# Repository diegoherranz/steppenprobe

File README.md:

# Steppenprobe
Open Source Hardware JTAG/SWD/UART/SWO interface board

https://github.com/diegoherranz/steppenprobe

## Basic specs:

- Open Source Hardware and designed in [KiCad](https://kicad.org).
- [FT2232H](https://ftdichip.com/products/ft2232hl)-based
- Simultaneous operation of JTAG/SWD and UART/SWO.
- STDC14 connector: standard Arm Cortex debug connector (1.27 mm pitch) with extra pins for UART. JTAG/SWD and UART on a single connector while being compatible with the standard Arm Cortex debug connector (middle 10 pins).
- USB powered: no power supply needed.
- USB type-C receptacle: more convenient (reversible) and future-proof (it should be the most common connector during the next few years).
- OpenOCD compatible, supported from version 0.11.0 (older versions can be used by adapting this [config file](https://sourceforge.net/p/openocd/code/ci/master/tree/tcl/interface/ftdi/steppenprobe.cfg) to the old sintax).
- JTAG or SWD use without any jumper or switch operation required (configured from OpenOCD).
- Switch-selectable UART RX or SWO operation.
- Signals also available on 2.54 mm pin header to work with any custom pinout.
- 4 GPIO.
- System Reset tactile switch.
- I/O buffers for protection and to be able to use a wide voltage range (1.65 V to 5.5 V).
- Descriptive LED indicators.

## Schematic PDF, Gerbers and other generated files:
See [releases](https://github.com/diegoherranz/steppenprobe/releases).

## FTDI channels

The FT2232H has 2 independent channels. In this board:

- Channel A: Used for JTAG or SWD (MPSSE mode) + GPIOs
- Channel B: Used as UART. TX+RX or TX+SWO depending on the position of the physical switch.

After enumeration, both channels will default to UART mode, so on a Linux system they will show up as `/dev/ttyUSB0` and `/dev/ttyUSB1`. When channel A gets reconfigured to MPSSE mode (e.g. when using OpenOCD with it), then `/dev/ttyUSB0` will disappear and channel B will remain as `/dev/ttyUSB1`.

## 3D renders

## Options for J2 connector (1.27 mm pitch header)
You can solder a 10-way or 14-way header depending on what suits you best:
 - 10-way header: [FTSH-105-01-F-DV-K](https://www.samtec.com/products/ftsh-105-01-f-dv-k) or equivalent. Use the central 10 pads in this case. JTAG, SWD, SWO and RESET (Arm Cortex debug connector standard).
 - 14-way header: [FTSH-107-01-F-DV-K](https://www.samtec.com/products/ftsh-107-01-f-dv-k) or equivalent. Compared to the 10 pin option, it adds UART TX and RX (STDC14 standard). This can still connect to targets with a 10-way header by using a 14-way to 10-way cable.

## OpenOCD example commands

### Flashing
Flashing [NuttX](https://nuttx.apache.org) to a [Blue Pill](https://stm32-base.org/boards/STM32F103C8T6-Blue-Pill.html) using JTAG:

```
openocd -f interface/ftdi/steppenprobe.cfg -f target/stm32f1x.cfg -c "program nuttx.bin 0x08000000 verify reset exit"
```

Same but using SWD:

```
openocd -f interface/ftdi/steppenprobe.cfg -c "transport select swd" -f target/stm32f1x.cfg -c "program nuttx.bin 0x08000000 verify reset exit"
```
All these examples use the default reset signals configuration. You may need to adjust it for your target board to work or even if it works, you may want to define it explicitely. See the [Reset Configuration chapter](http://openocd.org/doc-release/html/Reset-Configuration.html) of the OpenOCD documentation for more details.

You can do so directly on the OpenOCD command:

```
openocd -f interface/ftdi/steppenprobe.cfg -c "reset_config srst_only" -f target/stm32f1x.cfg -c "program nuttx.bin 0x08000000 verify reset exit"
```

or defining your board config file (your_board.cfg) which may look like this:

```
reset_config srst_only
source [find target/stm32f4x.cfg]
```

And then you do:

```
openocd -f interface/ftdi/steppenprobe.cfg -f your_board.cfg -c "program nuttx.bin 0x08000000 verify reset exit"
```

### Debugging
Debugging example for an STM32F4 target.

Start OpenOCD:
- JTAG: `openocd -f interface/ftdi/steppenprobe.cfg -f target/stm32f4x.cfg`
- SWD: `openocd -f interface/ftdi/steppenprobe.cfg -c "transport select swd" -f target/stm32f4x.cfg
`

On a different terminal:
```
$ gdb-multiarch your_code.elf # or gcc-arm-none-eabi depending on your system.

# Attach to OpenOCD
(gdb) target extended-remote localhost:3333

# Reset the boad
(gdb) monitor reset halt

# Load the code to flash
(gdb) load

# Start running
continue
```
Then use GDB as normal: see https://www.gnu.org/software/gdb/documentation/

### Debugging + SWO

Start OpenOCD in SWD mode and use the `tpiu config` command. Also, the UART switch should be in the "TX+SWO" position.

```
openocd -f interface/ftdi/steppenprobe.cfg -c "transport select swd" -f target/stm32f4x.cfg -c "tpiu config external uart off 168000000 115200"
```

The `tpiu config` command configures the ARM ITM module and the SWO output. In the command above, `16800000` represents the TRACECLKIN frequency (usually the same as HCLK), and `115200` is the frequency/baurate of the SWO line. Adjust both as desired. See the [OpenOCD documentation](http://openocd.org/doc-release/html/Architecture-and-Core-Commands.html#ARMv7_002dM-specific-commands
) for more info.

If the selected SWO frequency can't be achieved, OpenOCD will output a message like:

> Info : Can not obtain 115200 trace port frequency from 168000000 TRACECLKIN frequency, using 115147 instead

In this case, the frequency achieved is close enough, but pay attention in case it wasn't.

Then, on another terminal:
```
# configure the serial port speed
stty -F /dev/ttyUSB1 115200

# start the ITM decoder
./itmdump -f /dev/ttyUSB1 -d1 
```

Note: ITM decoder available [here](https://sourceforge.net/p/openocd/code/ci/master/tree/contrib/itmdump.c), just compile by doing `gcc itmdump.c -o itmdump`.

One of the advantages of using the SWO signal is that it can be faster than a standard UART, specially for slow core clock frequencies (see [this nice article](https://blog.japaric.io/itm/) for more info). To benefit from that, we need to use faster SWO frequencies.

The FT2232H is capable or running the UART up to 12 Mbps, but the configuration is more cumbersome for the fastest speeds.

On a recent Linux system, you can go up to 4 Mbps, configuring everything the same way as explained above for 115200 bps. On different OSes, you may not be able to go above 115200 bps or even 38400 bps.

For 4 Mbps:

```
openocd -f interface/ftdi/steppenprobe.cfg -c "transport select swd" -f target/stm32f4x.cfg -c "tpiu config external uart off 168000000 4000000"
```

On another terminal:
```
stty -F /dev/ttyUSB1 4000000
./itmdump -f /dev/ttyUSB1 -d1
```

To use even higher frequencies, up to the maximum of 12 MHz if your setup and cabling allows it, it's necessary to use setserial to alias 38400 bps to a custom divider. The base frequency of the FT2232H is 60 MHz, so for instance, for 12 MHz, the divisor must be set to 5.

```
openocd -f interface/ftdi/steppenprobe.cfg -c "transport select swd" -f target/stm32f4x.cfg -c "tpiu config external uart off 168000000 12000000"
```

On a different terminal:
```
setserial /dev/ttyUSB1 spd_cust divisor 5
stty -F /dev/ttyUSB1 38400
./itmdump -f /dev/ttyUSB1 -d1
```

### GPIO usage
There are 4 GPIOs available: GPIO_A to GPIO_D. By default they are High-Impedance (Z).

They can be set through OpenOCD by using `ftdi_set_signal name 0|1|z`. For example:
```
ftdi_set_signal GPIO_B 1
```

And similarly, they can be read using `ftdi_get_signal name`.

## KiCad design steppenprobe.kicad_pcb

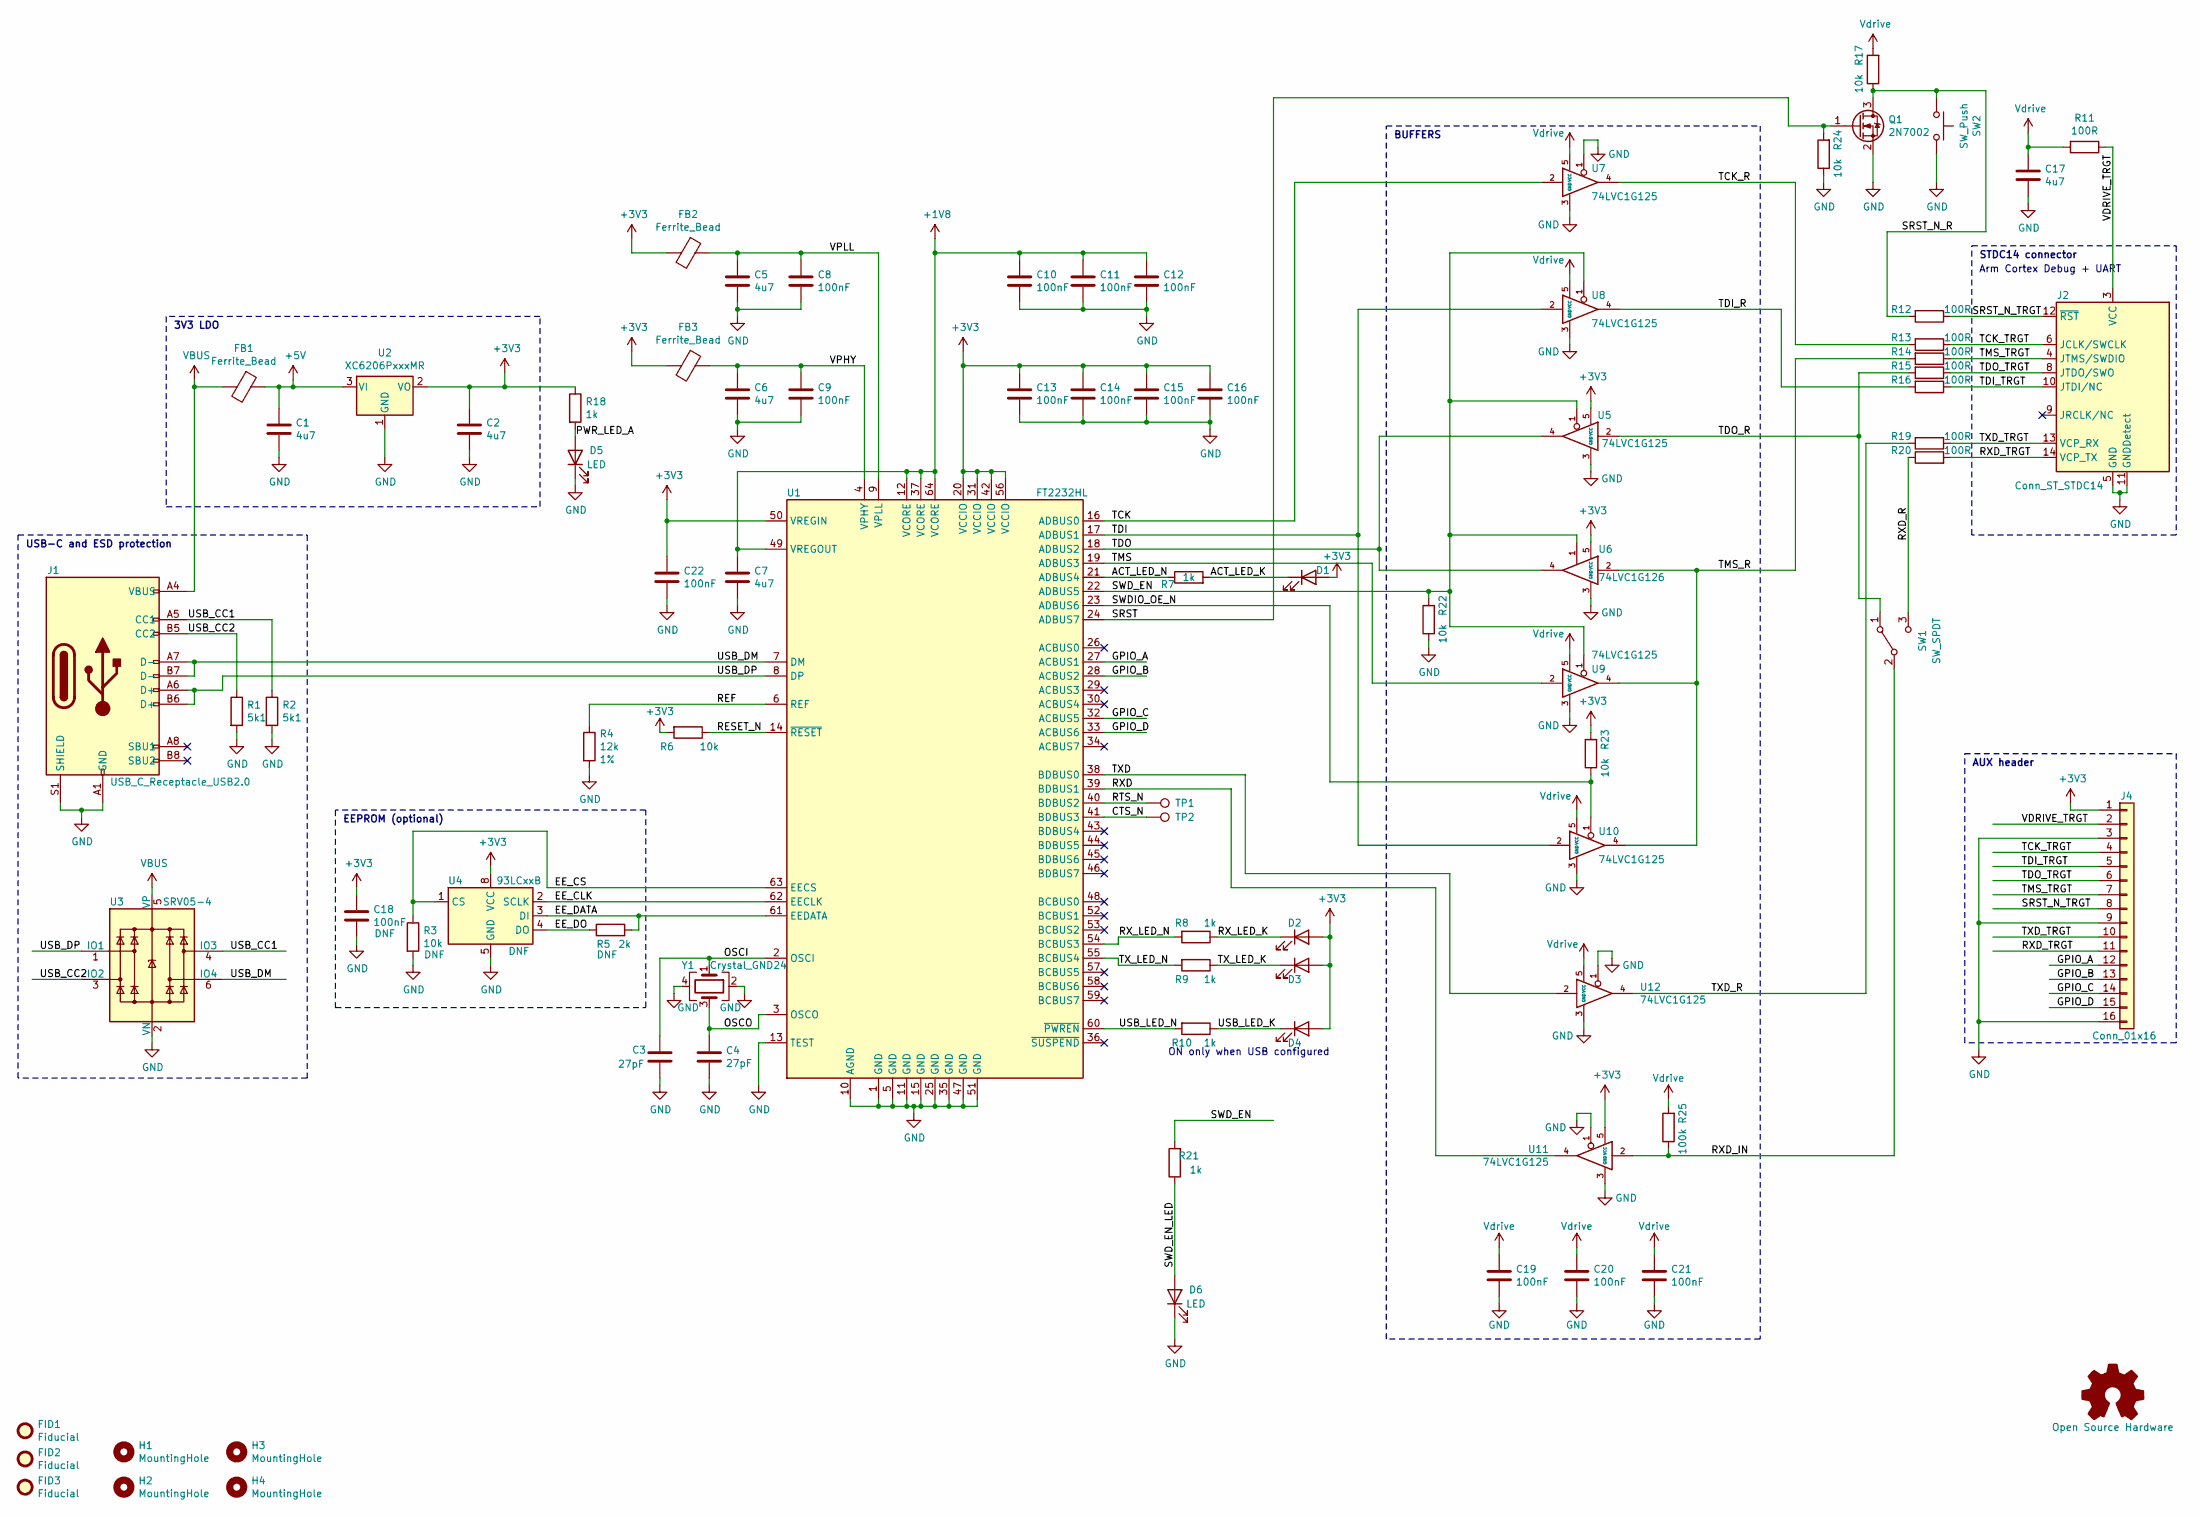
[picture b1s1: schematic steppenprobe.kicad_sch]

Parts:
C1, C2, C5, C6, C7, C17: 4u7; C_0603_1608Metric; Tolerance 10%; MPN CL10A475KO8NNNC; LCSC_PN C19666
C3, C4: 27pF; C_0603_1608Metric; Tolerance 5%; MPN C0603C270J5GAC; LCSC_PN C1656
C8, C9, C10, C11, C12, C13, C14, C15, C16, C19, C20, C21, C22: 100nF; C_0603_1608Metric; Tolerance 10%; MPN CC0603KRX7R9BB104; LCSC_PN C14663
C18: 100nF; C_0603_1608Metric
D1, D2, D3, D4, D5, D6: LED; LED_0603_1608Metric; MPN 19-217/GHC-YR1S2/3T; LCSC_PN C72043
FB1, FB2, FB3: Ferrite_Bead; L_0603_1608Metric; MPN2 BKP1608HS121-T; LCSC_PN C85831
FID1, FID2, FID3: Fiducial; Fiducial_1mm_Mask2mm
H1, H2, H3, H4: MountingHole; MountingHole_3.2mm_M3
J1: USB_C_Receptacle_USB2.0; USB_C_Receptacle_GCT_USB4085; MPN USB4085-GF-A
J2: Conn_ST_STDC14; PinHeader_2x07_P1.27mm_Vertical_SMD; MPN FTSH-107-01-F-DV-K (if 14-way)
J4: Conn_01x16; PinHeader_1x16_P2.54mm_Vertical; MPN M20-9991645
LOGO1: Open Source Hardware; OSHW-Logo_7.5x8mm_SilkScreen
Q1: 2N7002; SOT-23; MPN 2N7002-7-F; LCSC_PN C8545
R1, R2: 5k1; R_0603_1608Metric; Tolerance 5%; LCSC_PN C23186
R3: 10k; R_0603_1608Metric
R4: 12k; R_0603_1608Metric; Tolerance 1%; LCSC_PN C22790
R5: 2k; R_0603_1608Metric
R6, R17, R22, R23, R24: 10k; R_0603_1608Metric; Tolerance 5%; LCSC_PN C25804
R7, R8, R9, R10, R18, R21: 1k; R_0603_1608Metric; Tolerance 5%; LCSC_PN C21190
R11, R12, R13, R14, R15, R16, R19, R20: 100R; R_0603_1608Metric; Tolerance 5%; LCSC_PN C22775
R25: 100k; R_0603_1608Metric; Tolerance 5%; LCSC_PN C25803
SW1: SW_SPDT; SW_SPDT_PCM12; MPN EG1215AA
SW2: SW_Push; SW_Push_1P1T_NO_E-Switch_TL3301NxxxxxG; MPN PTS645SK43SMTR92 LFS
TP1, TP2: TestPoint; TestPoint_Pad_D1.0mm
U1: FT2232HL; LQFP-64_10x10mm_P0.5mm; MPN FT2232HL; LCSC_PN C27882
U2: XC6206PxxxMR; SOT-23; MPN XC6206P332MR; LCSC_PN C5446
U3: SRV05-4; SOT-23-6; MPN2 SRV05-4-P-T7; LCSC_PN C85364
U4: 93LCxxB; SOIC-8_3.9x4.9mm_P1.27mm
U5, U7, U8, U9, U10, U11, U12: 74LVC1G125; SOT-353_SC-70-5; MPN 74LVC1G125GW,125; LCSC_PN C12519
U6: 74LVC1G126; SOT-353_SC-70-5; MPN 74LVC1G126GW,125; LCSC_PN C55052
Y1: Crystal_GND24; Crystal_SMD_3225-4Pin_3.2x2.5mm; Tolerance 10PPM; MPN ABM8-12.000MHZ-20-B1U-T; LCSC_PN C9002

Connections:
+1V8: C7.1, C10.1, C11.1, C12.1, U1.12 (VCORE), U1.37 (VCORE), U1.49 (VREGOUT), U1.64 (VCORE)
+3V3: C2.1, C13.1, C14.1, C15.1, C16.1, C18.1, C22.1, D1.2 (A), D2.2 (A), D3.2 (A), D4.2 (A), FB2.2, FB3.2, J4.1, R6.2, R18.1, R23.2, U1.20 (VCCIO), U1.31 (VCCIO), U1.42 (VCCIO), U1.50 (VREGIN), U1.56 (VCCIO), U2.2 (VO), U4.8 (VCC), U5.5 (VCC), U6.5 (VCC), U11.5 (VCC)
+5V: C1.1, FB1.1, U2.3 (VI)
/ACT_LED_K: D1.1 (K), R7.2
/ACT_LED_N: R7.1, U1.21 (ADBUS4)
/CTS_N: TP2.1, U1.41 (BDBUS3)
/EE_CLK: U1.62 (EECLK), U4.2 (SCLK)
/EE_CS: R3.1, U1.63 (EECS), U4.1 (CS)
/EE_DATA: R5.2, U1.61 (EEDATA), U4.3 (DI)
/EE_DO: R5.1, U4.4 (DO)
/GPIO_A: J4.12, U1.27 (ACBUS1)
/GPIO_B: J4.13, U1.28 (ACBUS2)
/GPIO_C: J4.14, U1.32 (ACBUS5)
/GPIO_D: J4.15, U1.33 (ACBUS6)
/OSCI: C3.1, U1.2 (OSCI), Y1.1
/OSCO: C4.1, U1.3 (OSCO), Y1.3
/PWR_LED_A: D5.2 (A), R18.2
/REF: R4.1, U1.6 (REF)
/RESET_N: R6.1, U1.14 (~RESET)
/RTS_N: TP1.1, U1.40 (BDBUS2)
/RXD: U1.39 (BDBUS1), U11.4
/RXD_IN: R25.1, SW1.2 (B), U11.2
/RXD_R: R20.1, SW1.3 (C)
/RXD_TRGT: J2.14 (VCP_TX), J4.11, R20.2
/RX_LED_K: D2.1 (K), R8.1
/RX_LED_N: R8.2, U1.54 (BCBUS3)
/SRST: Q1.1 (G), R24.2, U1.24 (ADBUS7)
/SRST_N_R: Q1.3 (D), R12.2, R17.1, SW2.1
/SRST_N_TRGT: J2.12 (~RST), J4.8, R12.1
/SWDIO_OE_N: R23.1, U1.23 (ADBUS6), U10.1
/SWD_EN: R21.2, R22.2, U1.22 (ADBUS5), U5.1, U6.1, U8.1, U9.1
/SWD_EN_LED: D6.2 (A), R21.1
/TCK: U1.16 (ADBUS0), U7.2
/TCK_R: R13.2, U7.4
/TCK_TRGT: J2.6 (JCLK/SWCLK), J4.4, R13.1
/TDI: U1.17 (ADBUS1), U8.2, U10.2
/TDI_R: R16.2, U8.4
/TDI_TRGT: J2.10 (JTDI/NC), J4.5, R16.1
/TDO: U1.18 (ADBUS2), U5.4, U6.4
/TDO_R: R15.2, SW1.1 (A), U5.2
/TDO_TRGT: J2.8 (JTDO/SWO), J4.6, R15.1
/TMS: U1.19 (ADBUS3), U9.2
/TMS_R: R14.2, U6.2, U9.4, U10.4
/TMS_TRGT: J2.4 (JTMS/SWDIO), J4.7, R14.1
/TXD: U1.38 (BDBUS0), U12.2
/TXD_R: R19.2, U12.4
/TXD_TRGT: J2.13 (VCP_RX), J4.10, R19.1
/TX_LED_K: D3.1 (K), R9.1
/TX_LED_N: R9.2, U1.55 (BCBUS4)
/USB_CC1: J1.A5 (CC1), R2.1, U3.4 (IO3)
/USB_CC2: J1.B5 (CC2), R1.1, U3.3 (IO2)
/USB_DM: J1.A7 (D-), J1.B7 (D-), U1.7 (DM), U3.6 (IO4)
/USB_DP: J1.A6 (D+), J1.B6 (D+), U1.8 (DP), U3.1 (IO1)
/USB_LED_K: D4.1 (K), R10.1
/USB_LED_N: R10.2, U1.60 (~PWREN)
/VDRIVE_TRGT: J2.3 (VCC), J4.2, R11.1
/VPHY: C6.1, C9.1, FB3.1, U1.4 (VPHY)
/VPLL: C5.1, C8.1, FB2.1, U1.9 (VPLL)
GND: C1.2, C2.2, C3.2, C4.2, C5.2, C6.2, C7.2, C8.2, C9.2, C10.2, C11.2, C12.2, C13.2, C14.2, C15.2, C16.2, C17.2, C18.2, C19.2, C20.2, C21.2, C22.2, D5.1 (K), D6.1 (K), J1.A1 (GND), J1.A12 (GND), J1.B1 (GND), J1.B12 (GND), J1.S1 (SHIELD), J2.5 (GND), J2.7 (GND), J2.11 (GNDDetect), J4.3, J4.9, J4.16, Q1.2 (S), R1.2, R2.2, R3.2, R4.2, R22.1, R24.1, SW2.2, U1.1 (GND), U1.5 (GND), U1.10 (AGND), U1.11 (GND), U1.13 (TEST), U1.15 (GND), U1.25 (GND), U1.35 (GND), U1.47 (GND), U1.51 (GND), U2.1 (GND), U3.2 (VN), U4.5 (GND), U5.3 (GND), U6.3 (GND), U7.1, U7.3 (GND), U8.3 (GND), U9.3 (GND), U10.3 (GND), U11.1, U11.3 (GND), U12.1, U12.3 (GND), Y1.2, Y1.4
VBUS: FB1.2, J1.A4 (VBUS), J1.A9 (VBUS), J1.B4 (VBUS), J1.B9 (VBUS), U3.5 (VP)
Vdrive: C17.1, C19.1, C20.1, C21.1, R11.2, R17.2, R25.2, U7.5 (VCC), U8.5 (VCC), U9.5 (VCC), U10.5 (VCC), U12.5 (VCC)

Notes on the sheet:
EEPROM (optional)
ON only when USB configured
Arm Cortex Debug + UART
3V3 LDO
AUX header
STDC14 connector
USB-C and ESD protection
BUFFERS

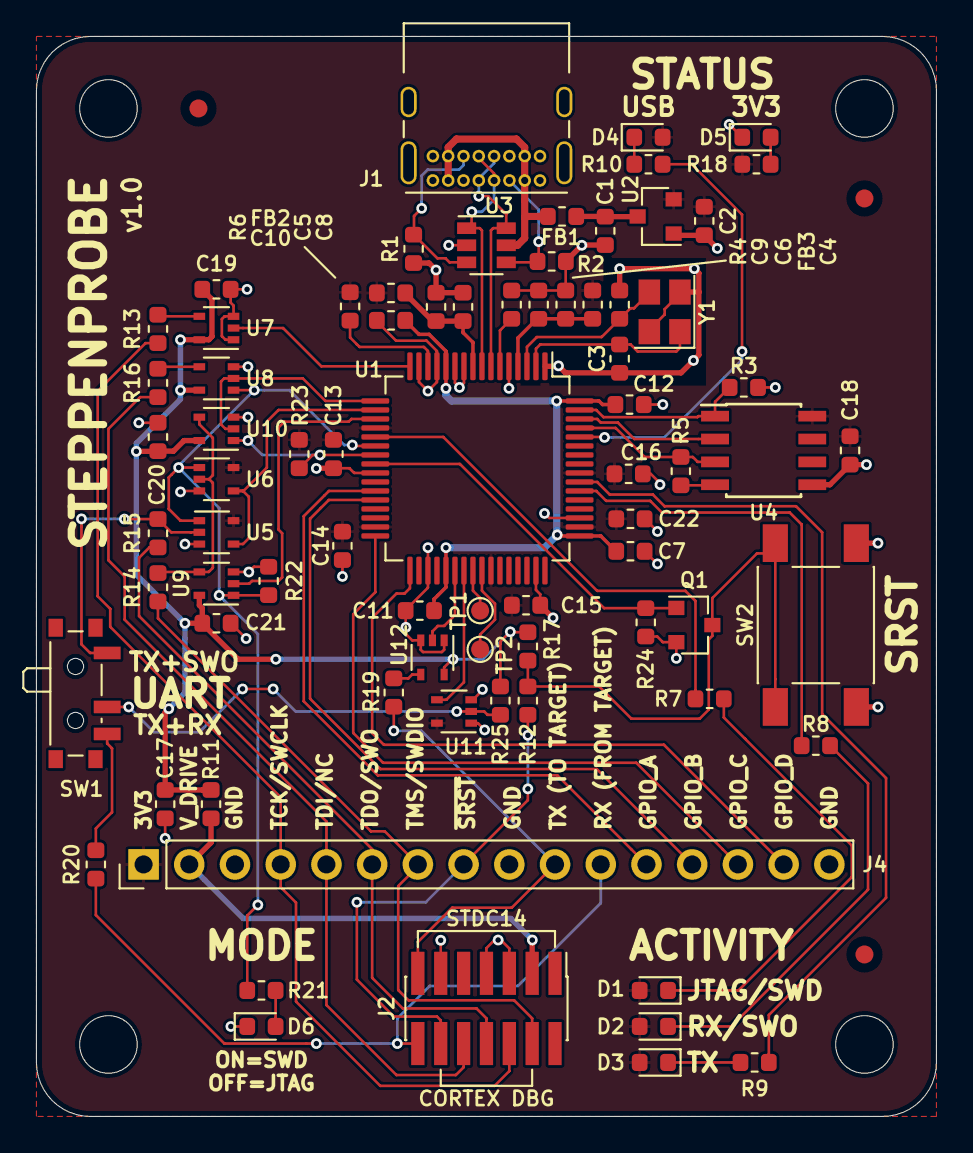
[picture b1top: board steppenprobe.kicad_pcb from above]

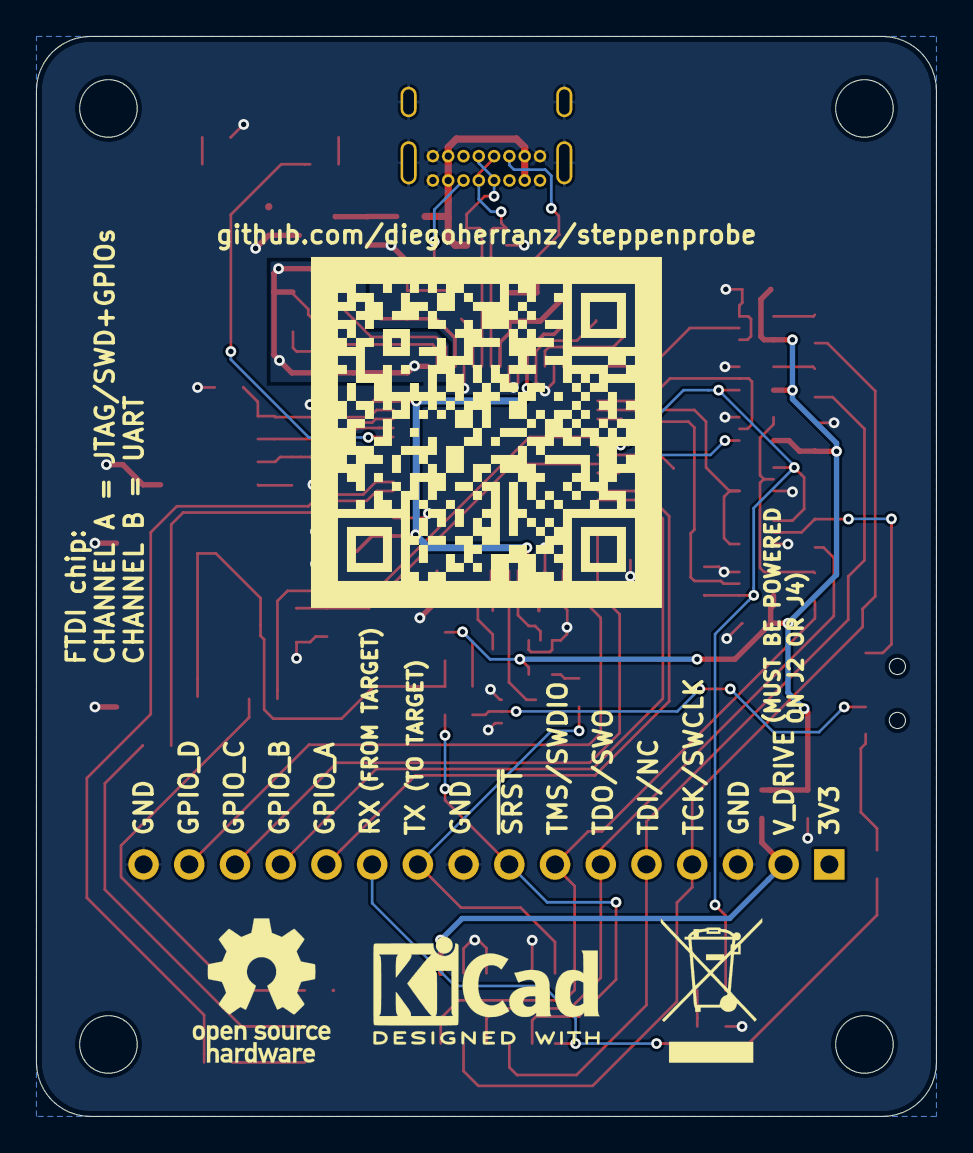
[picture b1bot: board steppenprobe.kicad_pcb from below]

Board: 2 copper layers, 50.0 x 60.0 mm, 86 parts (2 on the bottom side), 61 nets.

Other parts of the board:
QR*****: qr_steppenprobe_neg

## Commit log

2019-08-25 Initial commit
    Schematic basically ready but needs some tidying up
    Layout: approximate placement, tracking pending
2019-10-08 Progress placement.
    Most components placed.
    Most routing pending.
2019-10-13 SCH: Replace HC49 crystal by 3225
    Schematic only. Layout update pending.
2019-10-13 SCH: V_Drive_R for the 2.54mm header too
2019-10-13 PCB: reshuffle with new smaller crystal
2019-10-27 A few SCH changes:
    - add extra decoupling caps on V_DRIVE
    - Name net SWD_EN_LED
2019-10-27 Lot of progress on the layout
    Some notes:
    - Top plane/fill is now 3V3
    - Crystal fully routed
2019-10-29 SCH: add cap on VREGIN
2019-10-30 Layout routed completely. Needs clean-up and tidy-up.
2019-10-31 Some layout tidy-up
2019-10-31 Make MPSSE LED active low
    So that all the activity LEDs have the same orientation.
2019-11-02 Add pull up on SWDIO_OE and layout clean-up
    - To prevent the buffer to be active when the FTDI pin is High-Z.
    - Some cleanup including silkscreen and Fab
2019-11-02 Go v0.1
    Test this and only tag v1.0 when all OK
2019-11-03 Add many MPNs and LCSC PNs
2019-11-03 Replace LDO: MIC5504 -> XC6026
    Available on JLCPCB as Basic Part.
    Many alternative MPNs available for this new footprint, so not an issue.
2019-11-03 Use 4u7 caps for LDO input and output too
    Minimum size recommended is 1uF input and 1uF output.
    But given capacitance derating vs DC voltage, it is probably
    a good idea to go for a higher value. That reduces the number
    of MPNs too.
2019-11-04 Add many MPNs including alternatives
2019-11-16 Layout clean up
2019-11-16 Many layout clean ups including smaller tracks and vias
    Now 0.15mm tracks and 0.6mm/0.3mm vias by default.
2019-11-16 More small layout clean up
2019-11-17 Add KiCad logo + small improvements
2019-11-24 Rename project as Steppenprobe
2019-11-24 Add QR and new project URL. Finish bottom side silkscreen.
2019-12-01 Add a few more MPNs and tidy-up
2019-12-01 Add README and LICENSE
2019-12-01 Add PCB renders to README
2019-12-01 Add info about generated files
2019-12-15 Add pull down resistor to SWD_EN
    I thought that the LED on that net would keep the net low when the
    FTDI chip leaves reset, but the internal pull up is able to pull it
    to ~2.3V. So, external pull down needed.
2019-12-15 Add pulldown to SRST (also rename from SRST_N)
2019-12-15 Rename SWDIO_OE to SWDIO_OE_N
2019-12-15 Rename VDRIVE_R to VDRIVE_TRGT
2020-01-09 Tidy-up schematic.
2020-01-12 Swap activity led and reset output. Remap GPIOs. Plus some tidy up.
    - GPIOs only using pins which boot as input (with 75k pull up): GPIO0 was
    driven low on boot which can cause undesired effects. GPI03 booted as
    RXLED# which is an input with a PU on idle but it could togle low if the
    chip receives anything on RX (e.g. noise).
    - MPSSE_LED_N renamed as ACT_LED_N (shorter)
    - GPIO{0..3} renamed as GPIO_{A-D}: so that they are not confused with
2020-02-09 Replace reset switch and layout changes
    - Reset switch SW_Push_1P1T_NO_E-Switch_TL3301NxxxxxG instead of SW_SPST_PTS645.
    The old one is smaller and not compatible (or at least too tight) with many easily sourceable 6mm switches.
    The new footprint should be compatible with many more options including the previous PTS645.
    Some small tweaks were required around it given its slightly bigger size.
    - Version now v1.0
    - GPIO names changed from 0-3 to A-D
2020-02-22 Replace FT2232H by FT2232HL
    Old symbol is no longer in the library. It was a common symbol for
    both LQFP and QFN and it is now individual symbols for different
    packages.
2020-02-22 .gitignore: ignore output/
2020-02-23 Move 74xxGxx to a project library
    The symbols in the upstream libraries use hidden power pins which
    doesn't work in this design which needs different power rails on
    different instances.
    So far, a private modifed branch of the libraries was used. But,
    becasue the upstream library won't be fix until KiCad 6 for
    compatibility reasons, a project library has been created which
2020-04-11 Add pull up resistor to RXD_IN
    To avoid spurious RX when floating.
    Also some small tidy up of silkscreen designators.
2020-04-11 LED resistors: 470R -> 1k They were too bright. 1k may still be a bit too bright but if the current is reduced further, the LEDs which blink for brief instants, like the JTAG/SWD activity, get harder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
2020-04-12 Zones re-filled
2020-04-12 Small silkscreen tweaks
    - Lines drawn around J2 now to the centre of the pads
    - "STEPPENPROBE" and "v1.0" moved slightly south
2020-04-12 Tolerance and Type information added for BOM
2020-04-12 Add 10-way Samtec connector as alternative to the 14-way.
2020-04-12 Small schematic tidy-up
2020-04-12 Add bom.ini: configuration for KiBoM
2020-04-12 Tweak soldermask parameters
    Clearence: 50um
    Minimum width: 100um
    And re-fill zones.
2020-04-12 Update documentation images
2020-11-08 Small README updates
    - Make generated files section clearer
    - Put 3D renders into separate section
    - Fix some typos
2021-03-27 README update
    - Better 3D renders (including models for every component)
    - Add OpenOCD examples
    - Add information about 10 vs 14-way header
    - Small improvements
2021-06-13 README.md: more OpenOCD examples, extra info and tidy-up
    - More debugging examples: GDB, SWO, GPIO
    - Explanation of Channel A and B
    - Some re-ordering and tidy-up
2021-11-09 Update README.md
    https://forum.kicad.info/t/warning-avoid-all-links-to-kicad-pcb-org-use-kicad-org/31521
2021-12-25 Update project to KiCad 6.0.0 format
    It was using the interim 5.99 nightlies
2021-12-25 Some cleanup after converting to KiCad 6.0
    - Dangling tracks within pads
    - SRST track had a clearance violation next to FTDI's pin 48,
    by only a few microns. Touched slightly to fix it.
2024-07-15 Save files with KiCad 8.0.x
    No change done, just open and save using KiCad 8.0.x.
